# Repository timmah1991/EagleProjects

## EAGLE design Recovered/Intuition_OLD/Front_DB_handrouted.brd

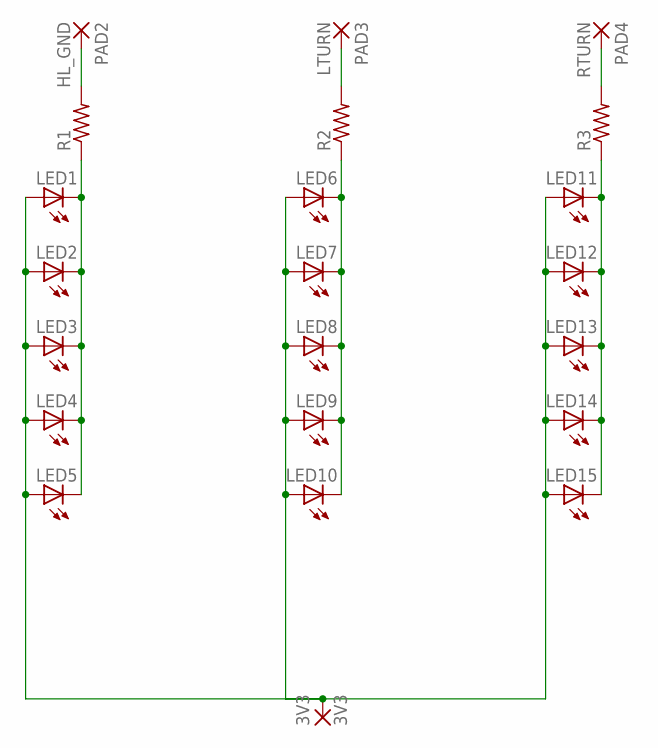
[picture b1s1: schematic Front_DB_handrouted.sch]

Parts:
3V3: 3V3; 2,54/1,1
LED1, LED2, LED3, LED4, LED5: LEDMICRO-SIDELED; MICRO-SIDELED
LED6, LED7, LED8, LED9, LED10, LED11, LED12, LED13, LED14, LED15: LEDCHIPLED_0603; CHIPLED_0603
PAD2: HL_GND; 2,54/1,1
PAD3: LTURN; 2,54/1,1
PAD4: RTURN; 2,54/1,1
R1, R2, R3: R-US_R0805; R0805

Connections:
unnamed: LED1.C, LED2.C, LED3.C, LED4.C, LED5.C, R1.1
unnamed: LED6.C, LED7.C, LED8.C, LED9.C, LED10.C, R2.1
unnamed: LED11.C, LED12.C, LED13.C, LED14.C, LED15.C, R3.1
unnamed: PAD4.1, R3.2
unnamed: PAD3.1, R2.2
unnamed: 3V3.1, LED1.A, LED2.A, LED3.A, LED4.A, LED5.A, LED6.A, LED7.A, LED8.A, LED9.A, LED10.A, LED11.A, LED12.A, LED13.A, LED14.A, LED15.A
unnamed: PAD2.1, R1.2

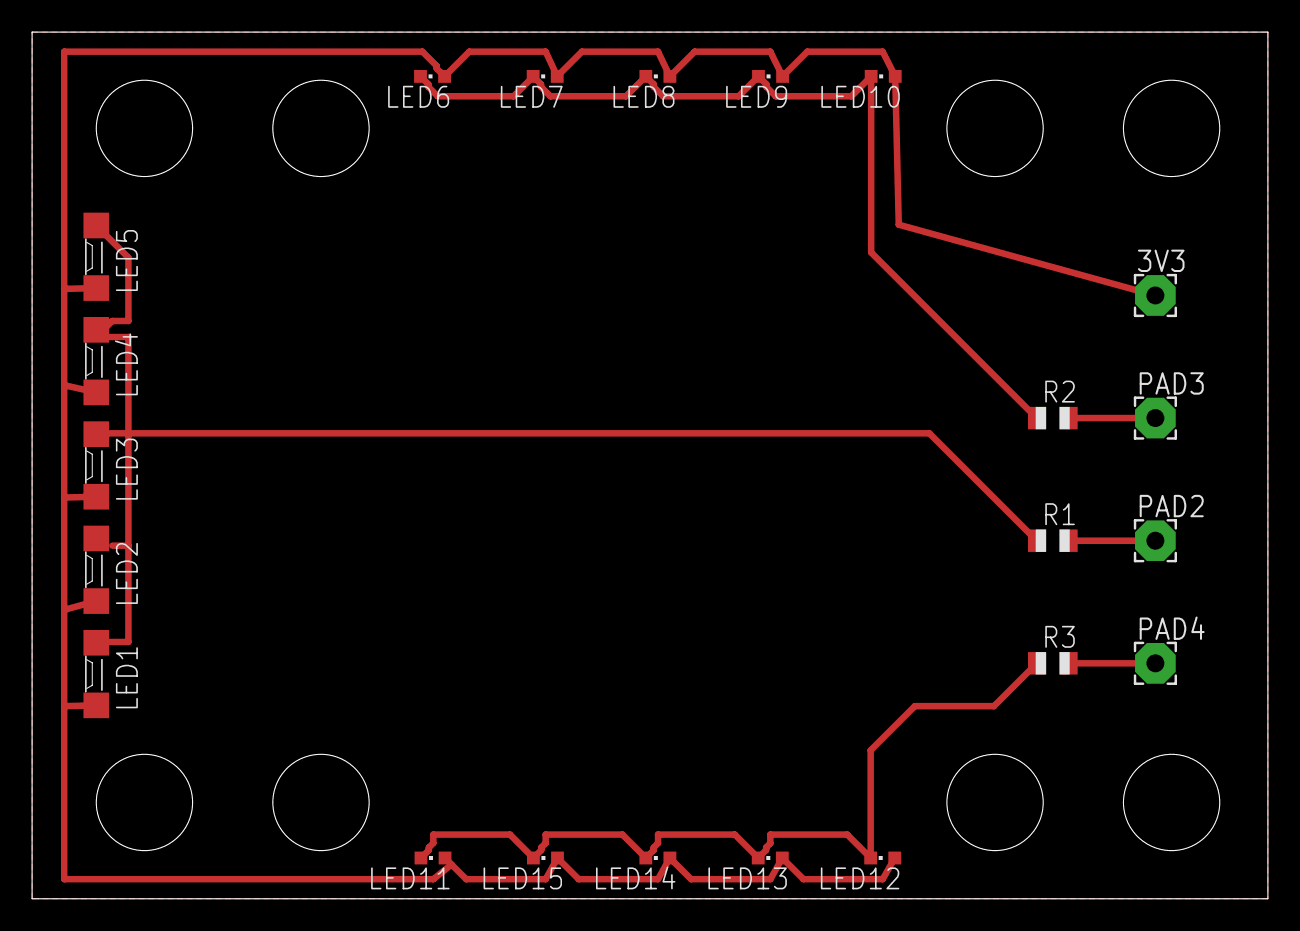
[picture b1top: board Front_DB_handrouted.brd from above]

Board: 2 copper layers, 77.0 x 54.0 mm, 22 parts (0 on the bottom side), 7 nets.

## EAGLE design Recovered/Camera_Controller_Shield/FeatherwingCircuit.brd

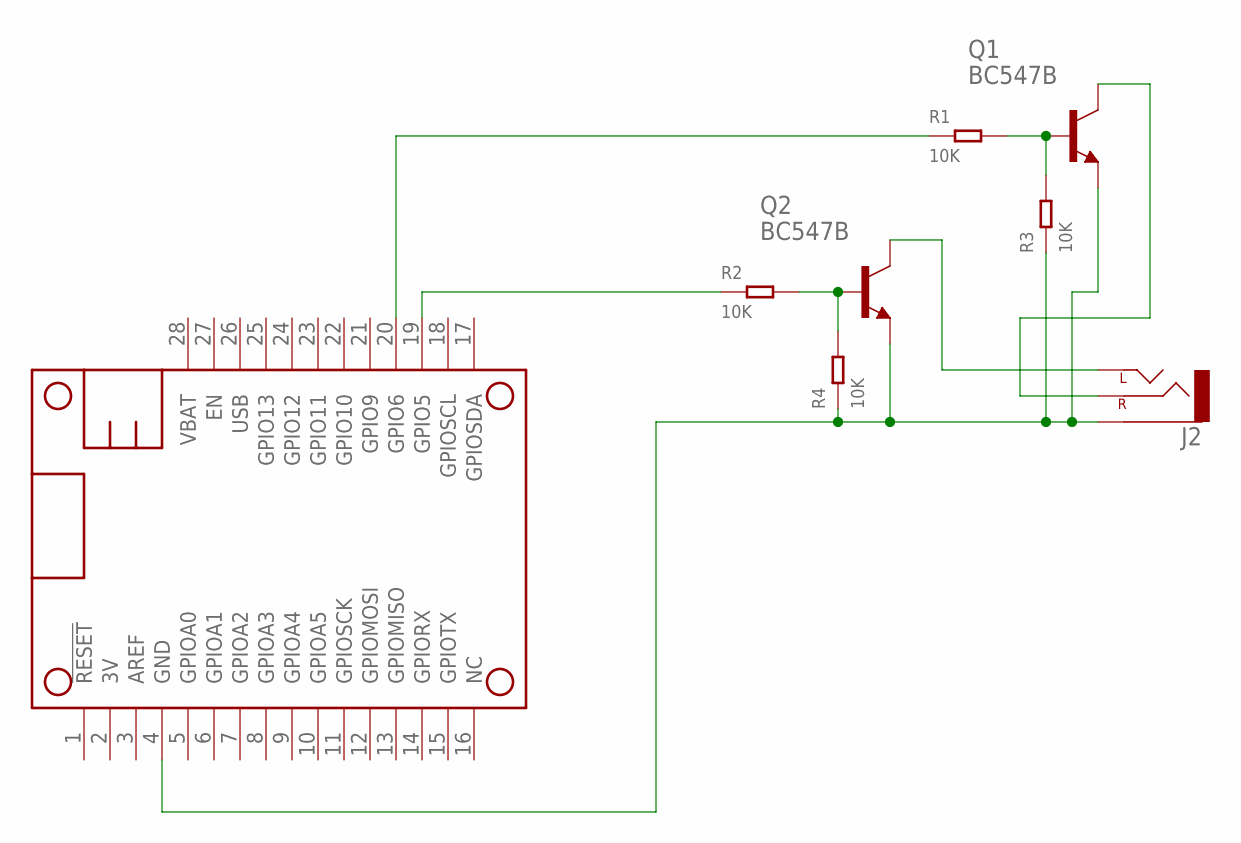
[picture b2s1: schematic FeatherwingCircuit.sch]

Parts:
J2: AUDIO_JACK_2.5MM_2.5MM; STEREOJACK2.5MM_STEREOJACK2.5MM
MS1: FEATHERWING_NODIM; FEATHERWING_DIM
Q1, Q2: BC547B; TO92
R1, R2, R3, R4: 10K; PR-D2.3XL6.5MM

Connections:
GND: J2.RING1 (SLEEVE), MS1.4 (GND), Q1.1 (E), Q2.1 (E), R3.1, R4.1
unnamed: Q1.2 (B), R1.2, R3.2
unnamed: Q2.2 (B), R2.2, R4.2
unnamed: J2.TIP (RIGHT), Q1.3 (C)
unnamed: J2.SHIELD (LEFT), Q2.3 (C)
unnamed: MS1.19 (GPIO5), R2.1
unnamed: MS1.20 (GPIO6), R1.1

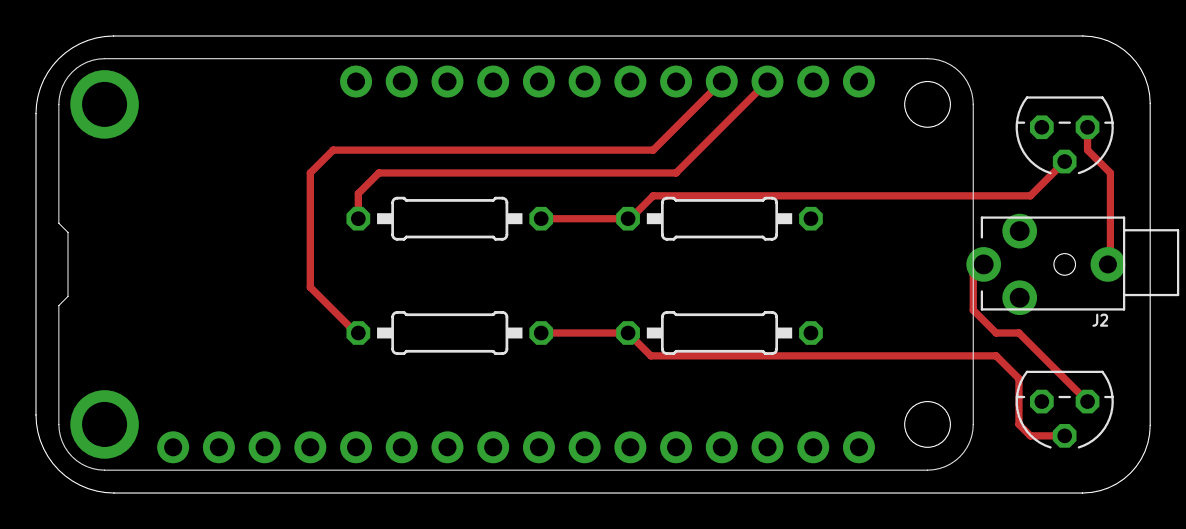
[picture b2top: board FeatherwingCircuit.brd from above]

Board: 2 copper layers, 61.9 x 25.4 mm, 8 parts (0 on the bottom side), 7 nets.

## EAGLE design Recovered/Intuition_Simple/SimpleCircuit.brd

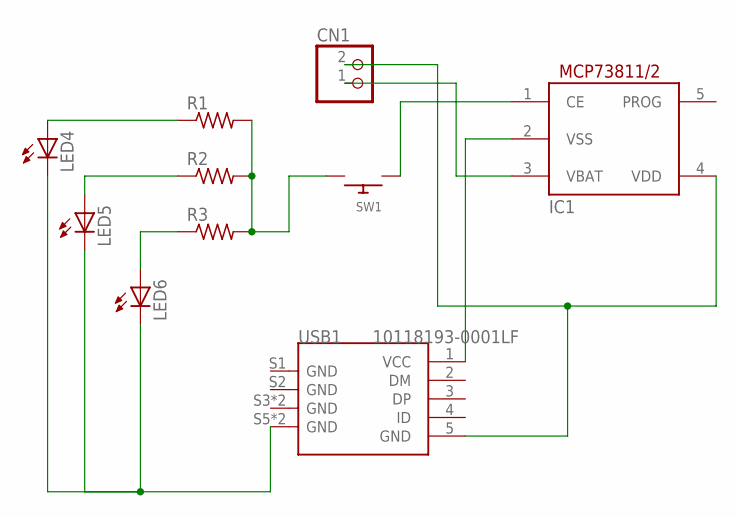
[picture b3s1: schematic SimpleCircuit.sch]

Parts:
CN1: JST_2PIN-SMT; JST-PH-2-SMT
IC1: MCP73811/2; SOT23-5L
LED4, LED5, LED6: LEDMICRO-SIDELED; MICRO-SIDELED
R1, R2, R3: R-US_R0805W; R0805W
SW1: SWITCH_PUSHBUTTONC&K_KSS; BTN_CK_KSS
USB1: 10118193-0001LF; MICRO-USB5+6P-SMD-0.65-B

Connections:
unnamed: R1.2, R2.2, R3.2, SW1.P$2
unnamed: LED4.A, R1.1
unnamed: LED5.A, R2.1
unnamed: LED6.A, R3.1
unnamed: IC1.2 (VSS), USB1.1 (VCC)
unnamed: CN1.2 (1), IC1.4 (VDD), USB1.5 (GND)
unnamed: LED4.C, LED5.C, LED6.C, USB1.S5 (GND), USB1.S6 (GND)
unnamed: IC1.1 (CE), SW1.P$1
unnamed: CN1.1 (2), IC1.3 (VBAT)

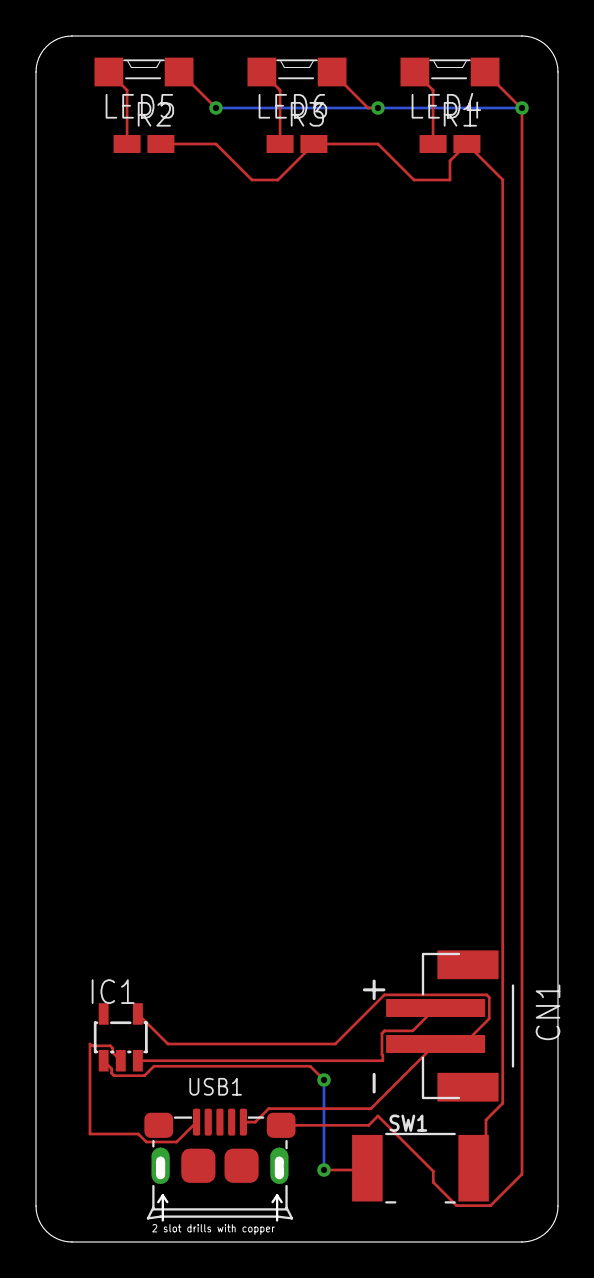
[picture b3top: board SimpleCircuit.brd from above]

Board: 2 copper layers, 28.5 x 66.5 mm, 10 parts (0 on the bottom side), 9 nets.

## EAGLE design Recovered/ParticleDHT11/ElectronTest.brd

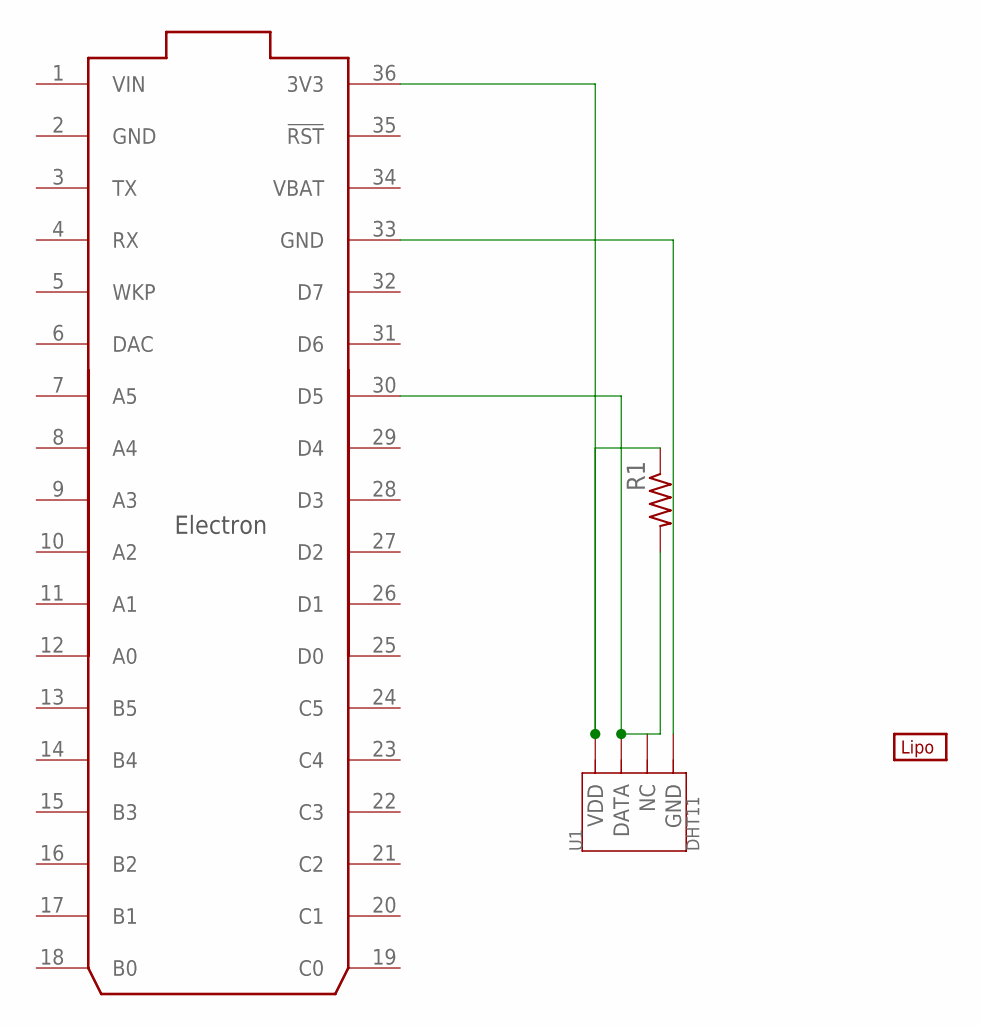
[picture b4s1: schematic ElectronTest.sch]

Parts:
BT1: LIPO-OUTLINE1100; LIPO-1000
R1: R-US_R2010W; R2010W
U1: DHT11; SNR4-2.54-15.5X12.0X5.5MM
U$1: ELECTRON_WITH_HEADERS; ELECTRON

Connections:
GND: U1.4 (GND), U$1.2 (GND), U$1.33 (GND)
unnamed: R1.2, U1.2 (DATA), U$1.30 (D5)
VBAT: U$1.34 (VBAT)
VDD: R1.1, U1.1 (VDD), U$1.36 (3V3)
VIN: U$1.1 (VIN)

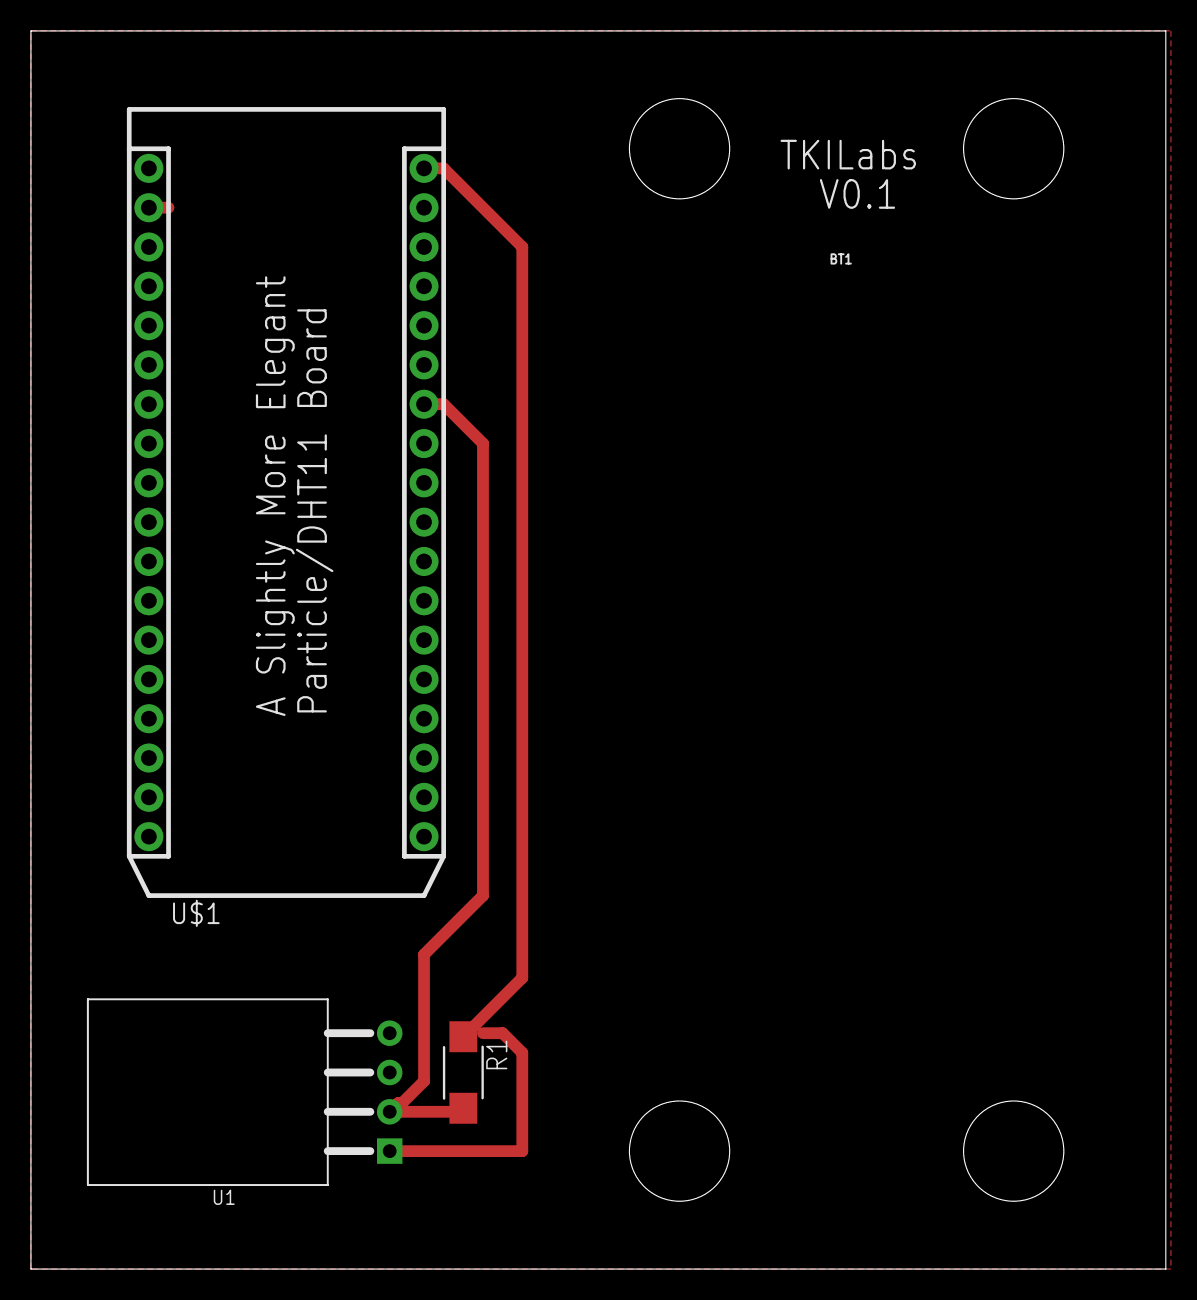
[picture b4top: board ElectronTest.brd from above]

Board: 2 copper layers, 73.3 x 80.0 mm, 4 parts (0 on the bottom side), 3 nets.

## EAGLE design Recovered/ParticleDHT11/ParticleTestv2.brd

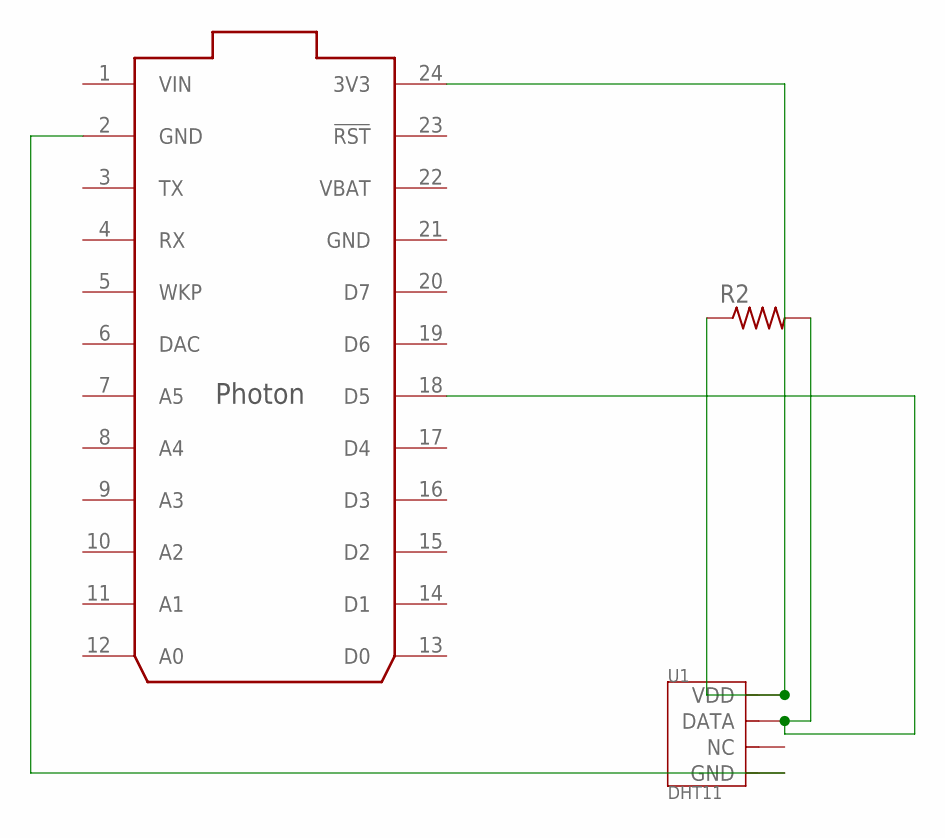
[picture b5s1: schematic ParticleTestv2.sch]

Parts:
R2: R-US_R0805; R0805
U1: DHT11; SNR4-2.54-15.5X12.0X5.5MM
U$1: PHOTON_WITH_HEADERS; PHOTON

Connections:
GND: U1.4 (GND), U$1.2 (GND), U$1.21 (GND)
unnamed: R2.2, U1.2 (DATA), U$1.18 (D5)
VBAT: U$1.22 (VBAT)
VDD: R2.1, U1.1 (VDD), U$1.24 (3V3)
VIN: U$1.1 (VIN)

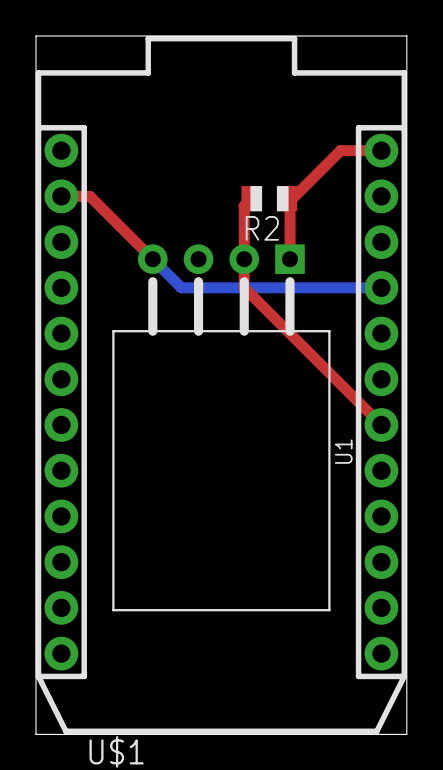
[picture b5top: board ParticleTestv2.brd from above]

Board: 2 copper layers, 20.6 x 38.8 mm, 3 parts (0 on the bottom side), 3 nets.

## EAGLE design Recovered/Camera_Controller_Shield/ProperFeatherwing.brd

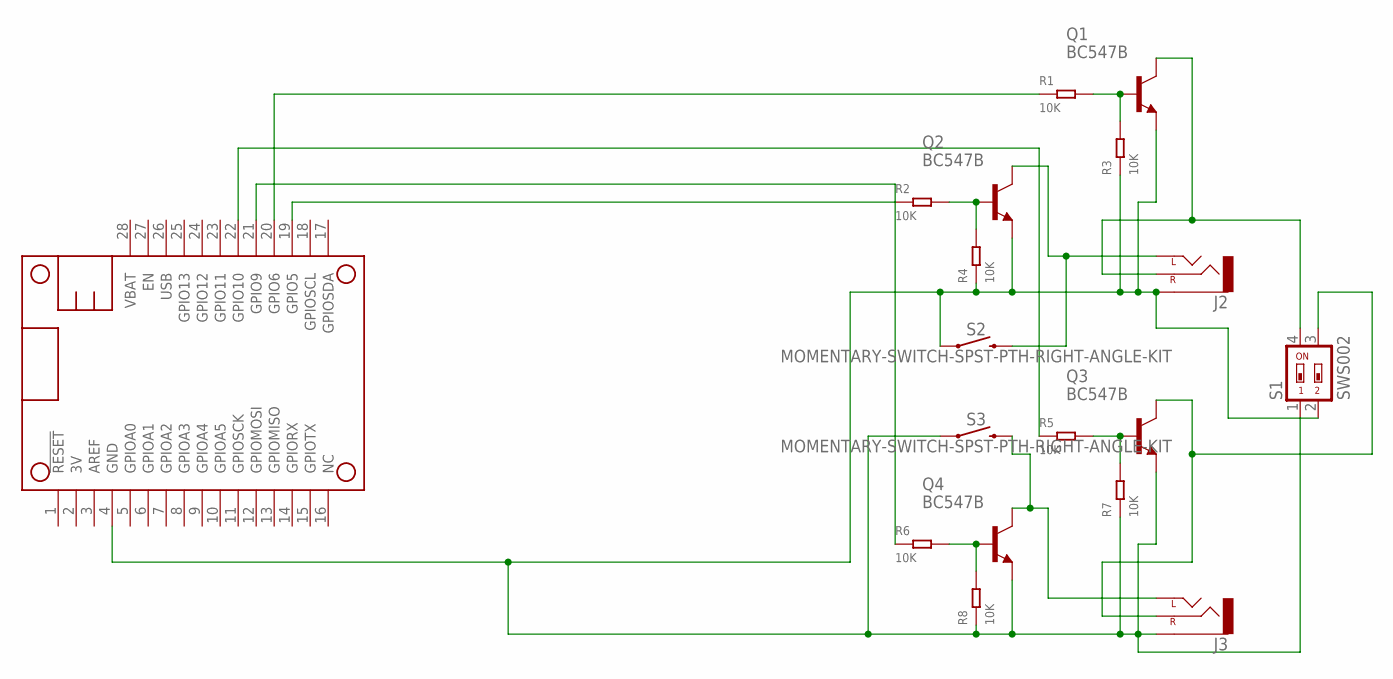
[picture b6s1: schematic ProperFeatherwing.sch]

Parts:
J2, J3: AUDIO_JACK_2.5MM_2.5MM; STEREOJACK2.5MM_STEREOJACK2.5MM
MS2: FEATHERWING
Q1, Q2, Q3, Q4: BC547B; TO92
R1, R2, R3, R4, R5, R6, R7, R8: 10K; PR-D2.3XL6.5MM
S1: SWS002; SMS-002
S2, S3: MOMENTARY-SWITCH-SPST-PTH-RIGHT-ANGLE-KIT; TACTILE_SWITCH_PTH_RIGHT_ANGLE_KIT

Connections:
GND: J2.RING1 (SLEEVE), J3.RING1 (SLEEVE), MS2.4 (GND), Q1.1 (E), Q2.1 (E), Q3.1 (E), Q4.1 (E), R3.1, R4.1, R7.1, R8.1, S1.1, S1.2, S2.1, S3.1
unnamed: Q1.2 (B), R1.2, R3.2
unnamed: Q2.2 (B), R2.2, R4.2
unnamed: J2.TIP (RIGHT), Q1.3 (C), S1.4
unnamed: J2.SHIELD (LEFT), Q2.3 (C), S2.2
unnamed: Q3.2 (B), R5.2, R7.2
unnamed: MS2.19 (GPIO5), R2.1
unnamed: MS2.20 (GPIO6), R1.1
unnamed: Q4.2 (B), R6.2, R8.2
unnamed: J3.TIP (RIGHT), Q3.3 (C), S1.3
unnamed: J3.SHIELD (LEFT), Q4.3 (C), S3.2
unnamed: MS2.21 (GPIO9), R6.1
unnamed: MS2.22 (GPIO10), R5.1

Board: 2 copper layers, 18 parts (0 on the bottom side), 13 nets, no tracks yet.

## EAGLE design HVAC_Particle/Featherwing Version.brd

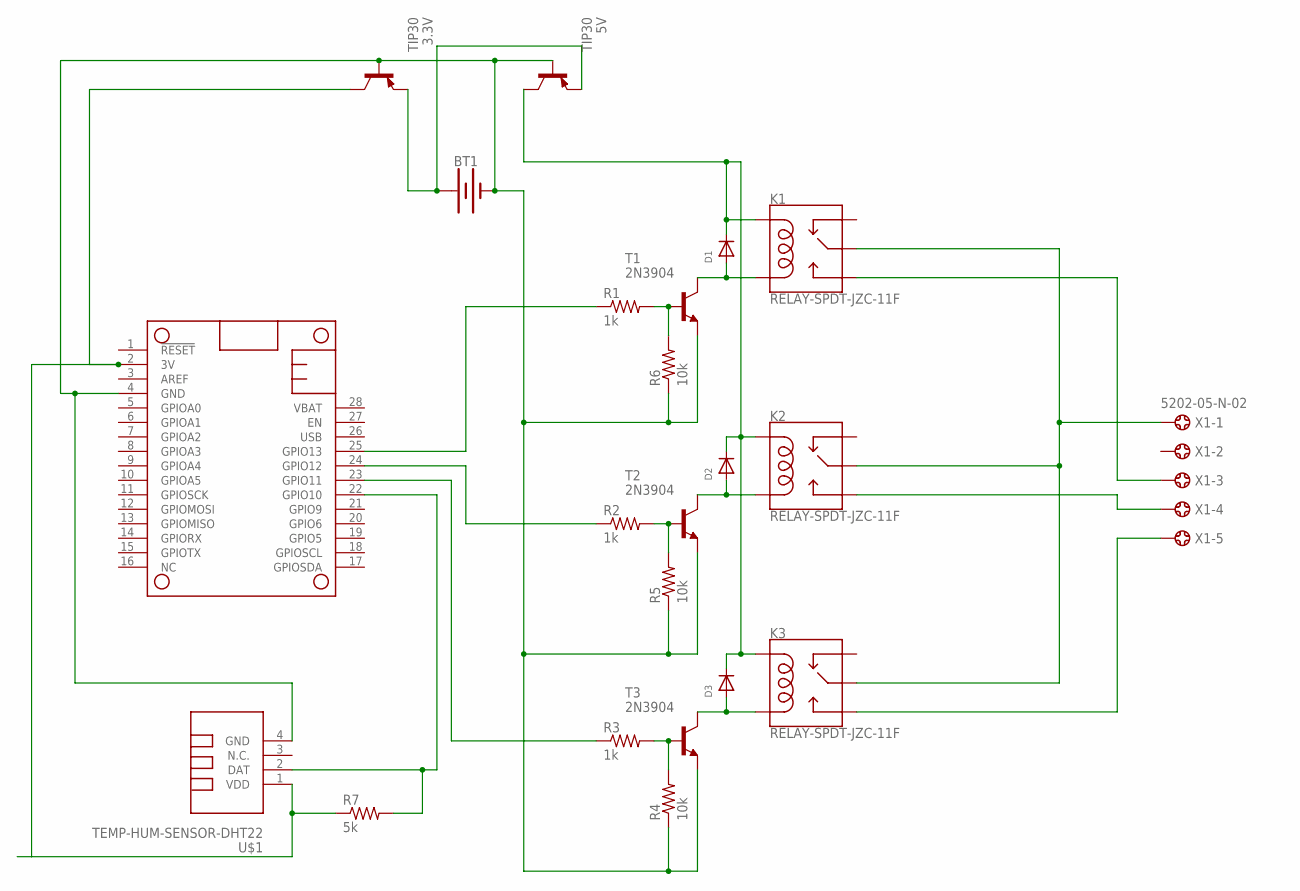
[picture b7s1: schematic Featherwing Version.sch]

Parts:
3.3V, 5V: TIP30; TO220
BT1: BATTERY-9V; BATTCON_9V
D1, D2, D3: DIODEDO-1N4148; DO-1N4148
K1, K2, K3: RELAY-SPDT-JZC-11F; RELAY-JZC
MS2: FEATHERWING
R1, R2, R3: 1k; 0309/10
R4, R5, R6: 10k; 0309/10
R7: 5k; 0309/10
T1, T2, T3: 2N3904; TO92
U$1: TEMP-HUM-SENSOR-DHT22
X1: 5202-05-N-02

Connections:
3V: 3.3V.2 (C), MS2.2 (3V), R7.1, U$1.1 (VDD)
unnamed: MS2.22 (GPIO10), R7.2, U$1.2 (DAT)
unnamed: D2.A, K2.1 (COIL2), T2.1 (C)
unnamed: D3.A, K3.1 (COIL2), T3.1 (C)
unnamed: 5V.2 (C), D1.C, D2.C, D3.C, K1.5 (COIL1), K2.5 (COIL1), K3.5 (COIL1)
unnamed: D1.A, K1.1 (COIL2), T1.1 (C)
unnamed: K1.4 (MAIN), K2.4 (MAIN), K3.4 (MAIN), X1.1
unnamed: K1.3 (NO), X1.3
unnamed: K2.3 (NO), X1.4
unnamed: K3.3 (NO), X1.5
unnamed: R3.2, R4.2, T3.2 (B)
unnamed: R2.2, R5.2, T2.2 (B)
unnamed: R1.2, R6.2, T1.2 (B)
unnamed: 3.3V.1 (B), 5V.1 (B), BT1.-, MS2.4 (GND), R4.1, R5.1, R6.1, T1.3 (E), T2.3 (E), T3.3 (E), U$1.4 (GND)
unnamed: 3.3V.3 (E), 5V.3 (E), BT1.+
unnamed: MS2.25 (GPIO13), R1.1
unnamed: MS2.24 (GPIO12), R2.1
unnamed: MS2.23 (GPIO11), R3.1

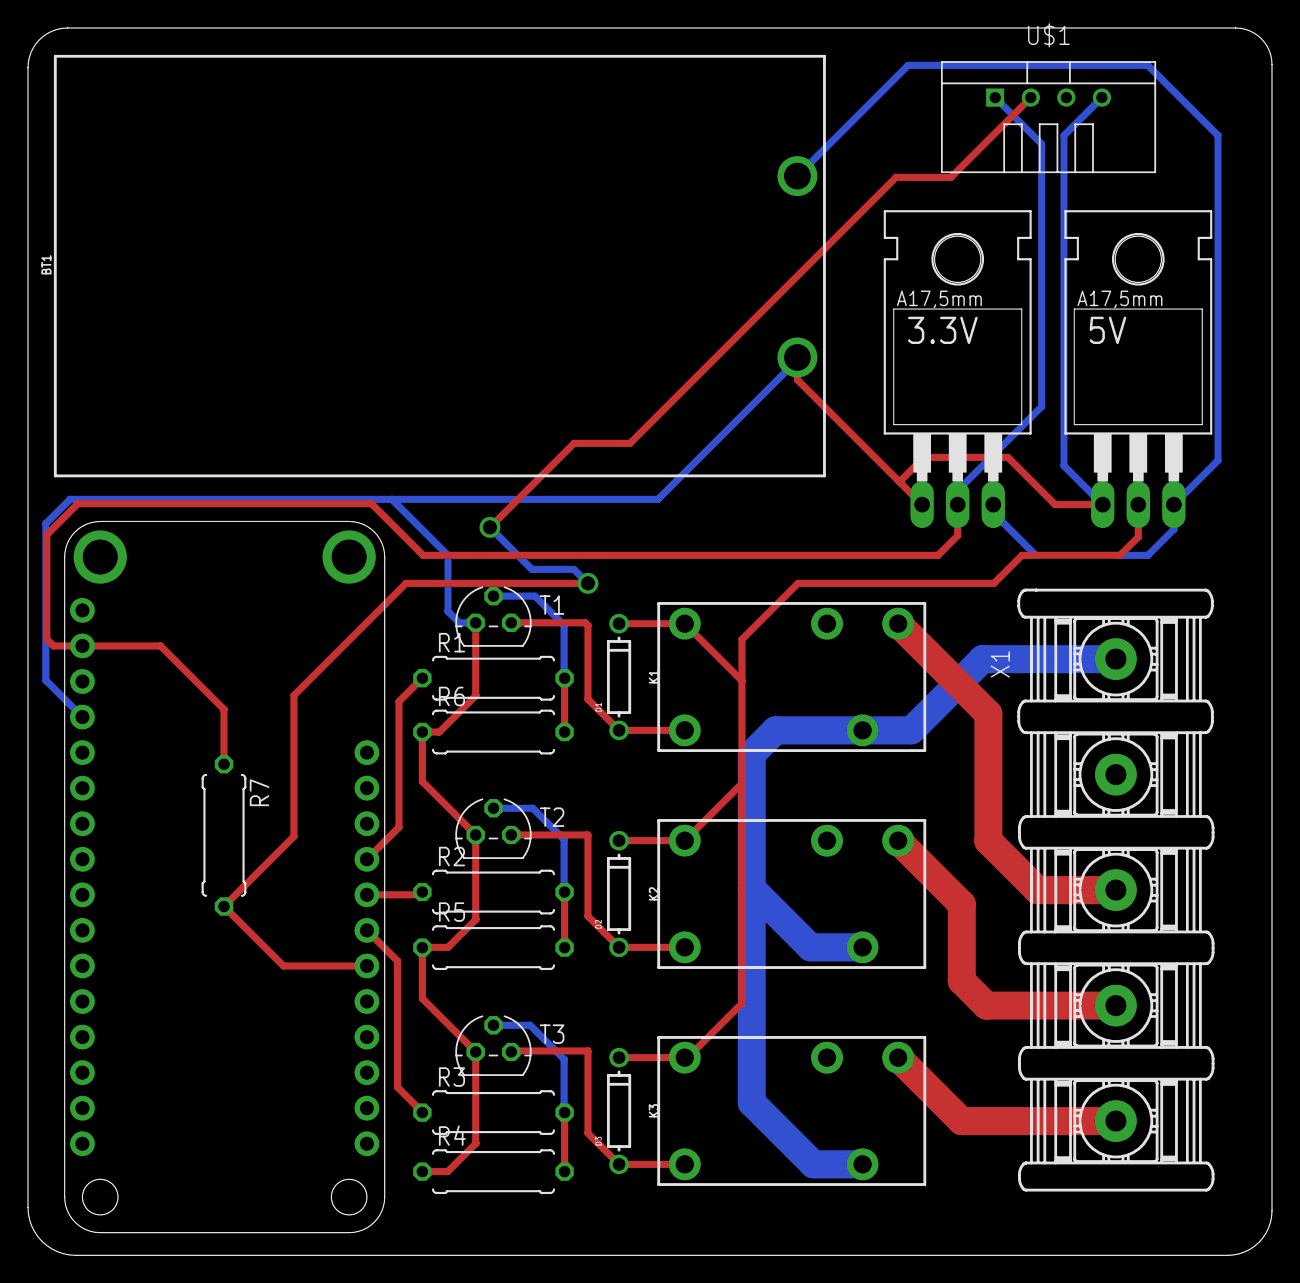
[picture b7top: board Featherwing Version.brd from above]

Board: 2 copper layers, 88.9 x 87.7 mm, 22 parts (0 on the bottom side), 18 nets.

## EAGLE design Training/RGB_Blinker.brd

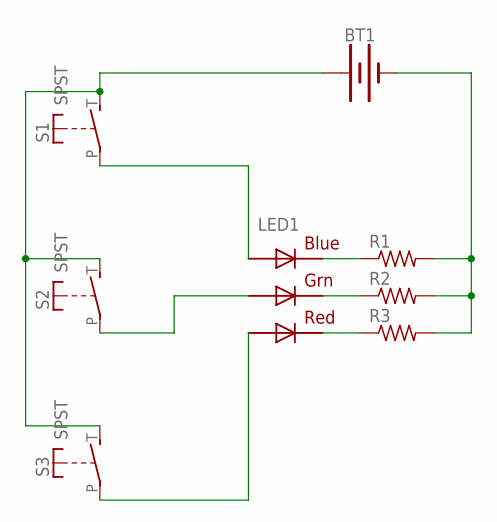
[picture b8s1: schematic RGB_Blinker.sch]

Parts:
BT1: BATTERY-20MM_SMD; BATTCON_20MM
LED1: RGBLED5050
R1, R2, R3: R-US_M2012; M2012
S1, S2, S3: SPST; JUDCOSPST

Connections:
unnamed: BT1.1 (+), S1.T (S), S2.T (S), S3.T (S)
unnamed: LED1.6 (GREEN_C), R2.1
unnamed: LED1.4 (BLUE_C), R1.1
unnamed: LED1.5 (RED_C), R3.1
unnamed: BT1.2 (-), R1.2, R2.2, R3.2
unnamed: LED1.3 (BLUE_A), S1.P
unnamed: LED1.2 (RED_A), S3.P
unnamed: LED1.1 (GREEN_A), S2.P

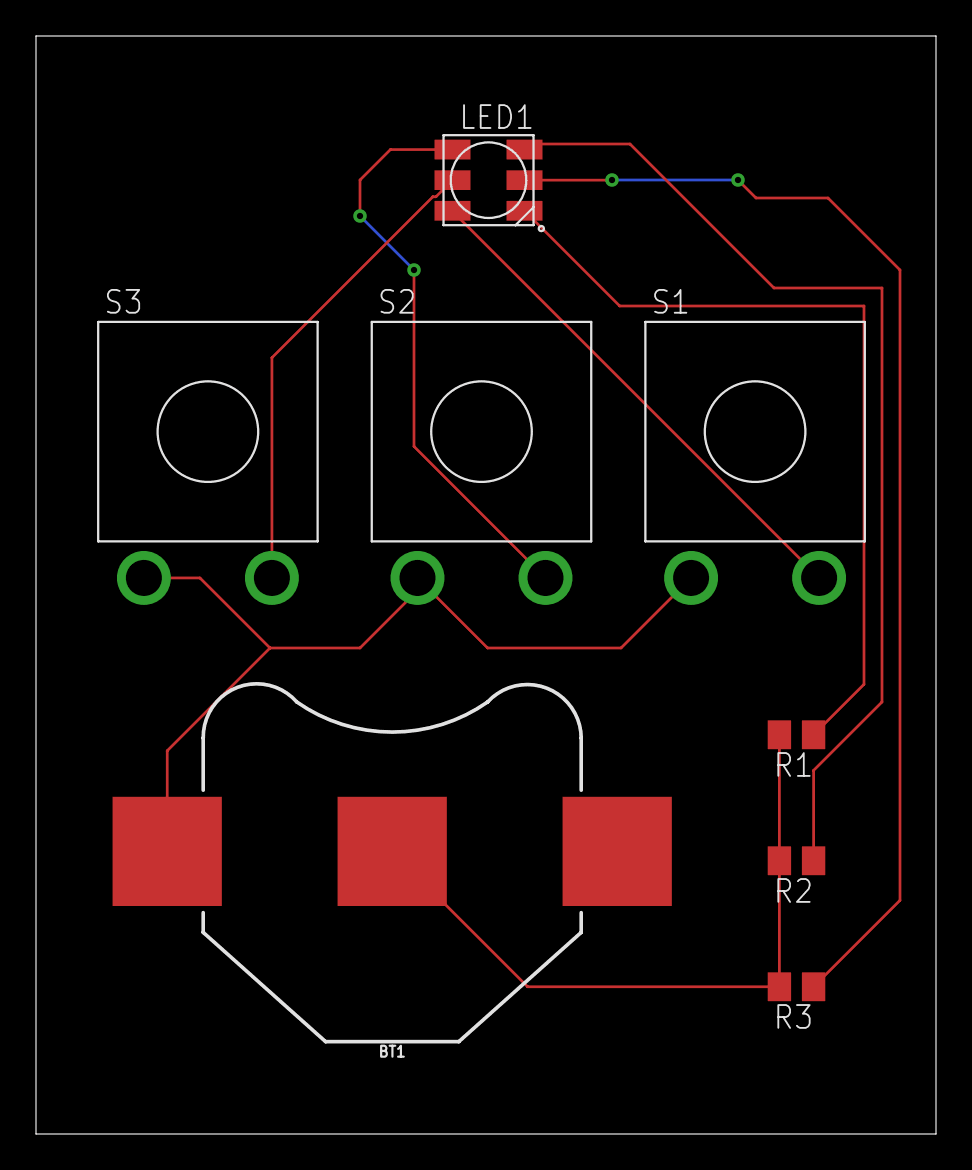
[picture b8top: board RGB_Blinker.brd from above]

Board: 2 copper layers, 50.0 x 61.0 mm, 8 parts (0 on the bottom side), 8 nets.

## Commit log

2019-05-03 adding Eagle projects
2019-05-22 added recovered EAGLE files

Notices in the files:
parts and their libraries:
SparkFun-Batteries: Licensing: Creative Commons ShareAlike 4.0 International - https://creativecommons.org/licenses/by-sa/4.0
diy-modules: Released under the Creative Commons Attribution 4.0 International License: http://creativecommons.org/licenses/by/4.0
